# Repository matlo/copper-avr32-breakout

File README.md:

# AVR32 Breakout "Copper"

A breakout board for the AVR32 UC3B series of
processors. Specifically, the UC3B1256, a 48 pin part with 256KiB of
Flash (http://www.atmel.com/devices/AT32UC3B1256.aspx).

The year was 2009, and the Cortex-M3 was just a glimmer on some
product roadmaps. Yet Atmel delivered a 32-bit micro-controller which
was really efficient, had good performance, and was easy to use.

Modern designs should use a well-supported Cortex-M series part (M3,
M4, M0)

# Features

 * AVR 32 UC3B156
 * Mini-B USB connector
 * Breadboard-compatible pin pitch
 * All pins (except USB) broken out to the headers
 * JTAG connector
 * Reset button
 * Green LED :-)

# License

Creative Commons 3.0 Share-Alike Unported

# Design Status

This design was in larger (100-unit lots) production and was sold as a
pre-assembled kit.

## Boards available

A limited number of boards are available. Send an e-mail to
yann@stackfoundry.com with your mailing address. US postage is free,
International will be dealt with as it happens :-)

Boards will be populated with processors if they are available.

# Files available

The original design is available as Eagle 6.x (XML-based) design
files, in the eagle/ directory.

Gerber files from the Eagle board file are made available in the
gerber/ directory.

Schematic PDF is available in the root of this repository.

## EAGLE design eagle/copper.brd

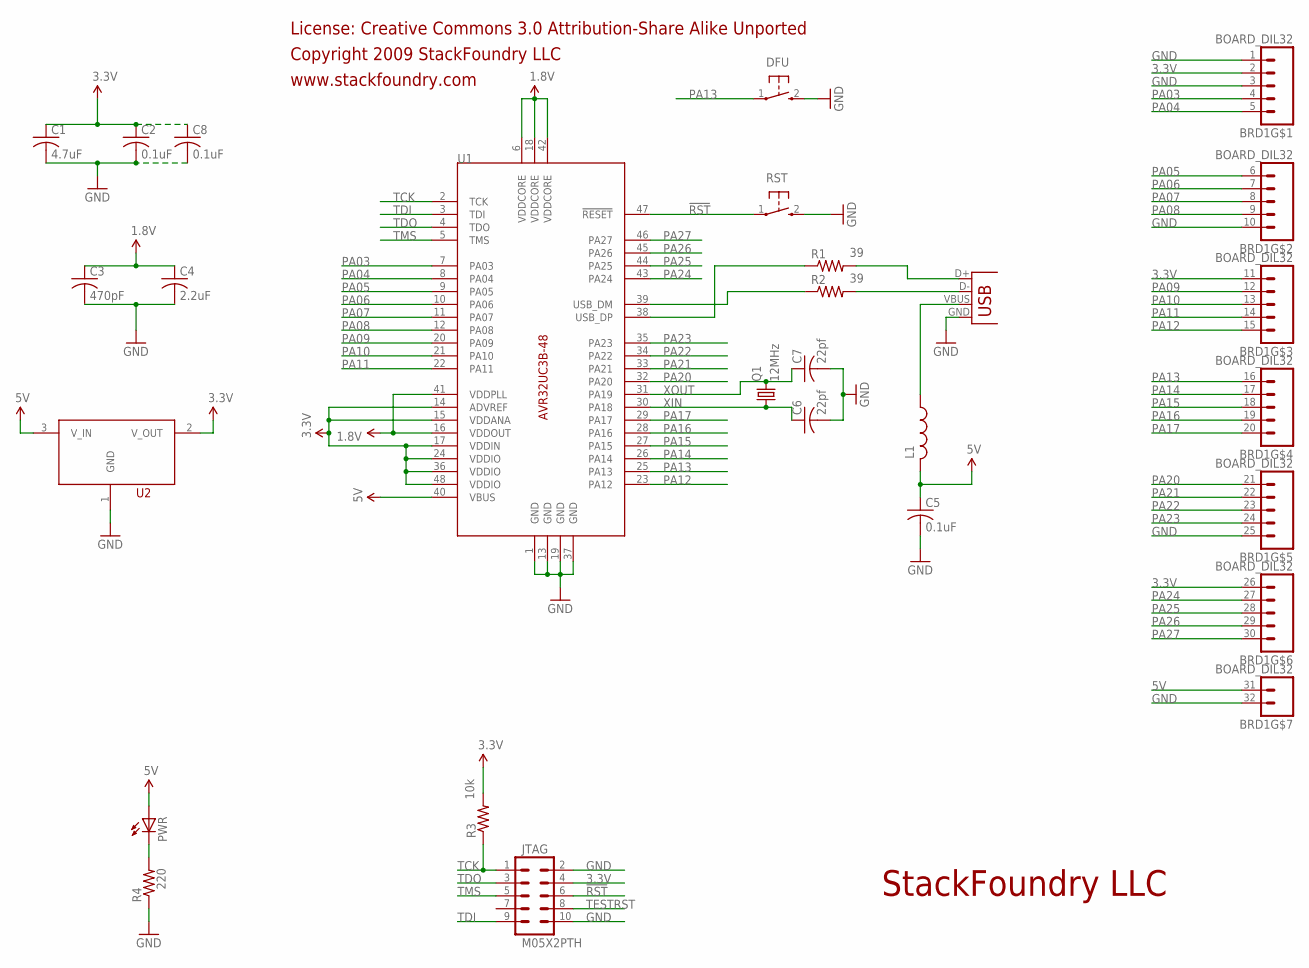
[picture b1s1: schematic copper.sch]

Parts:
BRD1: BOARD_DIL32; DIL32-NOSILK
C1: 4.7uF; C0603
C2, C5, C8: 0.1uF; C0603
C3: 470pF; C0603
C4: 2.2uF; C0603
C6, C7: 22pf; C0603
DFU: TAC_SWITCH_2PB3U; OMROM_B3U
JTAG: M05X2PTH; AVR_ICSP
L1: L-USL0805; L0805
PWR: LED1206; LED-1206
Q1: 12MHz; CRYSTAL-SMD-5X3.2
R1, R2: 39; R0603
R3: 10k; R0603
R4: 220; R0603
RST: TAC_SWITCH_2PB3U; OMROM_B3U
U1: AVR32UC3B-48TQFP; TQFP48
U2: MCP1700; SOT23
X2: USBSMD; USB-MINIB

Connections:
1.8V: C3.1, C4.1, U1.6 (VDDCORE), U1.16 (VDDOUT), U1.18 (VDDCORE), U1.41 (VDDPLL), U1.42 (VDDCORE)
3.3V: BRD1.2, BRD1.11 (1), BRD1.26 (1), C1.1, C2.1, C8.1, JTAG.4, R3.2, U1.14 (ADVREF), U1.15 (VDDANA), U1.17 (VDDIN), U1.24 (VDDIO), U1.36 (VDDIO), U1.48 (VDDIO), U2.2 (V_OUT)
5V: BRD1.31 (1), C5.1, L1.2, PWR.A, U1.40 (VBUS), U2.3 (V_IN)
!RST: JTAG.6, RST.1, U1.47 (!RESET)
GND: BRD1.1, BRD1.3, BRD1.10 (5), BRD1.25 (5), BRD1.32 (2), C1.2, C2.2, C3.2, C4.2, C5.2, C6.2, C7.2, C8.2, DFU.2 (3), JTAG.2, JTAG.10, R4.1, RST.2 (3), U1.1 (GND), U1.13 (GND), U1.19 (GND), U1.37 (GND), U2.1 (GND), X2.GND
unnamed: R1.1, U1.38 (USB_DP)
unnamed: R2.1, U1.39 (USB_DM)
unnamed: L1.1, X2.VBUS
unnamed: R1.2, X2.D+
unnamed: R2.2, X2.D-
unnamed: PWR.C, R4.2
PA03: BRD1.4, U1.7 (PA03)
PA04: BRD1.5, U1.8 (PA04)
PA05: BRD1.6 (1), U1.9 (PA05)
PA06: BRD1.7 (2), U1.10 (PA06)
PA07: BRD1.8 (3), U1.11 (PA07)
PA08: BRD1.9 (4), U1.12 (PA08)
PA09: BRD1.12 (2), U1.20 (PA09)
PA10: BRD1.13 (3), U1.21 (PA10)
PA11: BRD1.14 (4), U1.22 (PA11)
PA12: BRD1.15 (5), U1.23 (PA12)
PA13: BRD1.16 (1), DFU.1, U1.25 (PA13)
PA14: BRD1.17 (2), U1.26 (PA14)
PA15: BRD1.18 (3), U1.27 (PA15)
PA16: BRD1.19 (4), U1.28 (PA16)
PA17: BRD1.20 (5), U1.29 (PA17)
PA20: BRD1.21 (1), U1.32 (PA20)
PA21: BRD1.22 (2), U1.33 (PA21)
PA22: BRD1.23 (3), U1.34 (PA22)
PA23: BRD1.24 (4), U1.35 (PA23)
PA24: BRD1.27 (2), U1.43 (PA24)
PA25: BRD1.28 (3), U1.44 (PA25)
PA26: BRD1.29 (4), U1.45 (PA26)
PA27: BRD1.30 (5), U1.46 (PA27)
TCK: JTAG.1, R3.1, U1.2 (TCK)
TDI: JTAG.9, U1.3 (TDI)
TDO: JTAG.3, U1.4 (TDO)
TESTRST: JTAG.8
TMS: JTAG.5, U1.5 (TMS)
XIN: C6.1, Q1.1, U1.30 (PA18)
XOUT: C7.1, Q1.3 (2), U1.31 (PA19)

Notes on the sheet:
License: Creative Commons 3.0 Attribution-Share Alike Unported
Copyright 2009 StackFoundry LLC
www.stackfoundry.com
StackFoundry LLC

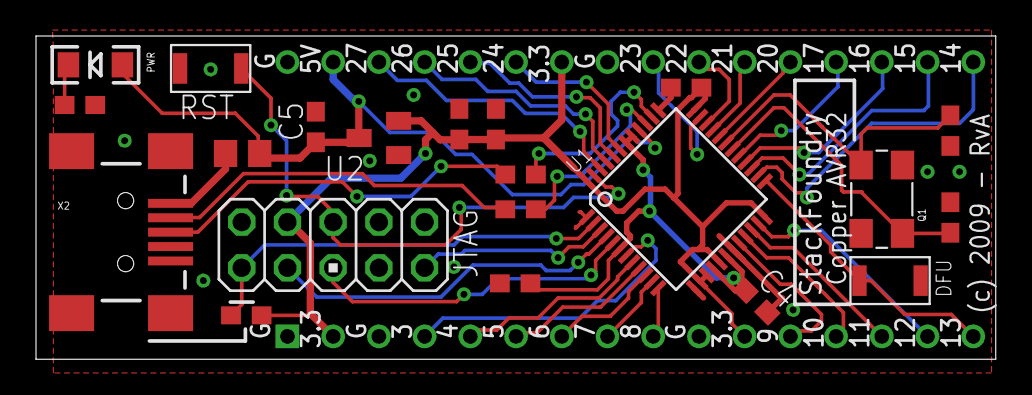
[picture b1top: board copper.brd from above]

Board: 2 copper layers, 53.3 x 18.0 mm, 22 parts (0 on the bottom side), 40 nets.

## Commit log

2009-10-26 Copper schematic
2009-10-26 Fix crystal
2009-10-26 Gerber data
2014-04-07 Re-arrange files
2014-04-07 Add artwork
2014-04-07 Add readme
2014-04-07 Fix typo

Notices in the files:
eagle/copper.brd:
(c) 2009 - RvA
